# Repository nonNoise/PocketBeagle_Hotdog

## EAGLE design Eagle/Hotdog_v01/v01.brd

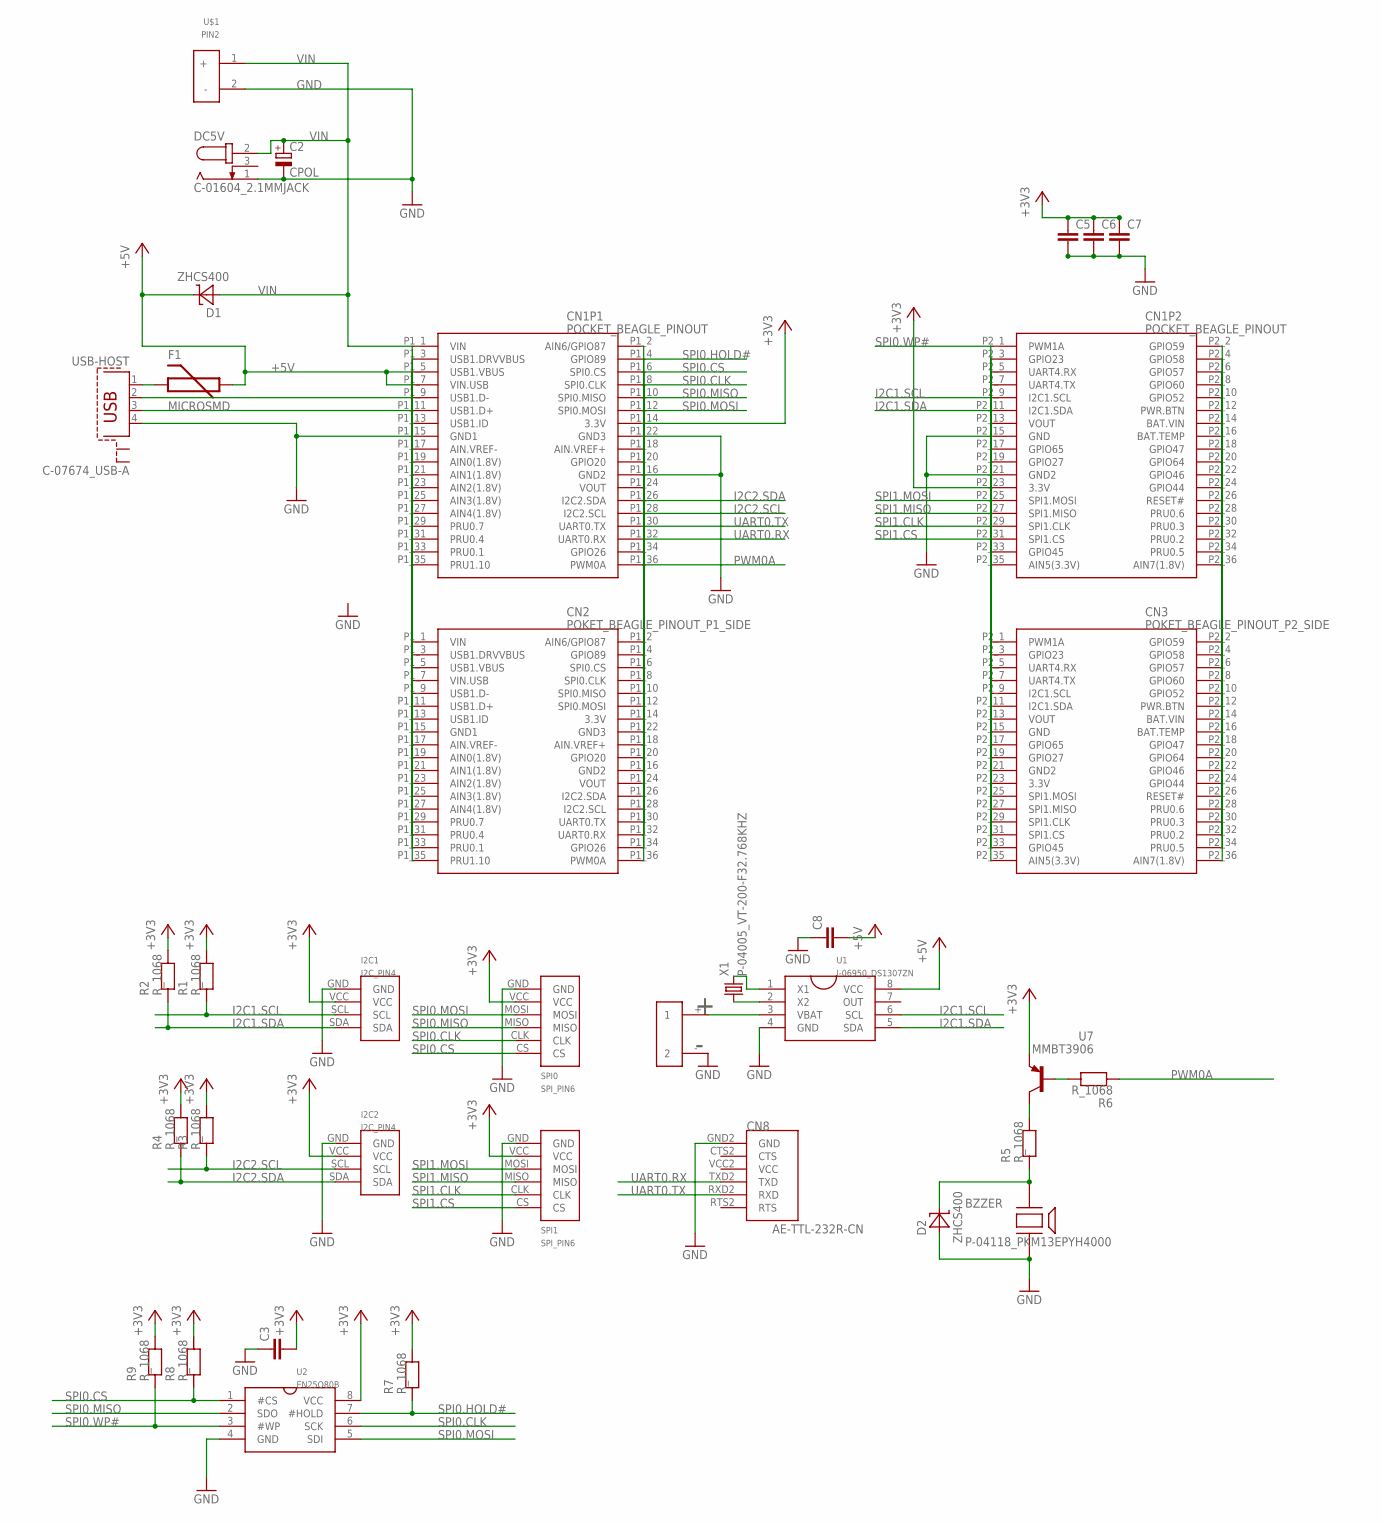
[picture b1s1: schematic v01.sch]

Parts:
BZZER: P-04118_PKM13EPYH4000; PKM13EPYH4000
C2: CPOL; 153CLV-0605
C3, C6, C7, C8: C_1068; C0603
C5: C_2012; C0805K
CN1: POCKET_BEAGLE_PINOUT
CN2: POKET_BEAGLE_PINOUT_P1_SIDE
CN3: POKET_BEAGLE_PINOUT_P2_SIDE
CN8: AE-TTL-232R-CN
CR2032: P-00706_CH25-2032LF; CH25-2032LF
D1, D2: ZHCS400; SOD323-W
DC5V: C-01604_2.1MMJACK; 2.1MMJACK
F1: MICROSMD
I2C1, I2C2: I2C_PIN4
R1, R2, R3, R4, R5, R6, R7, R8, R9: R_1068; R0603
SPI0, SPI1: SPI_PIN6
U1: I-06950_DS1307ZN; SO8
U2: EN25Q80B; SO8
U7: MMBT3906; SOT23
U$1: PIN2
USB-HOST: C-07674_USB-A; PN87520-S
X1: P-04005_VT-200-F32.768KHZ; VT-200F

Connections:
+3V3: C3.2, C5.1, C6.1, C7.1, CN1.P1_14 (3.3V), CN1.P2_23 (3.3V), CN2.P1_14 (3.3V), CN3.P2_23 (3.3V), I2C1.VCC, I2C2.VCC, R1.2, R2.2, R3.2, R4.2, R7.2, R8.2, R9.2, SPI0.VCC, SPI1.VCC, U2.8 (VCC), U7.2 (E)
+5V: C8.2, CN1.P1_5 (USB1.VBUS), CN1.P1_7 (VIN.USB), CN2.P1_5 (USB1.VBUS), CN2.P1_7 (VIN.USB), D1.C, F1.P$2, U1.8 (VCC)
GND: BZZER.2, C2.-, C3.1, C5.2, C6.2, C7.2, C8.1, CN1.P1_15 (GND1), CN1.P1_16 (GND2), CN1.P1_22 (GND3), CN1.P2_15 (GND), CN1.P2_21 (GND2), CN2.P1_15 (GND1), CN2.P1_16 (GND2), CN2.P1_22 (GND3), CN3.P2_15 (GND), CN3.P2_21 (GND2), CN8.GND2 (GND), CR2032.- (2), D2.A, DC5V.1 (GND), I2C1.GND, I2C2.GND, SPI0.GND, SPI1.GND, U1.4 (GND), U2.4 (GND), U$1.2 (-), USB-HOST.4
I2C1.SCL: CN1.P2_9 (I2C1.SCL), CN3.P2_9 (I2C1.SCL), I2C1.SCL, R1.1, U1.6 (SCL)
I2C1.SDA: CN1.P2_11 (I2C1.SDA), CN3.P2_11 (I2C1.SDA), I2C1.SDA, R2.1, U1.5 (SDA)
I2C2.SCL: CN1.P1_28 (I2C2.SCL), CN2.P1_28 (I2C2.SCL), I2C2.SCL, R3.1
I2C2.SDA: CN1.P1_26 (I2C2.SDA), CN2.P1_26 (I2C2.SDA), I2C2.SDA, R4.1
unnamed: CN1.P1_35 (PRU1.10), CN2.P1_35 (PRU1.10)
unnamed: CN1.P1_33 (PRU0.1), CN2.P1_33 (PRU0.1)
unnamed: CN1.P1_31 (PRU0.4), CN2.P1_31 (PRU0.4)
unnamed: CN1.P1_29 (PRU0.7), CN2.P1_29 (PRU0.7)
unnamed: CN1.P1_27 (AIN4(1.8V)), CN2.P1_27 (AIN4(1.8V))
unnamed: CN1.P1_25 (AIN3(1.8V)), CN2.P1_25 (AIN3(1.8V))
unnamed: CN1.P1_23 (AIN2(1.8V)), CN2.P1_23 (AIN2(1.8V))
unnamed: CN1.P1_21 (AIN1(1.8V)), CN2.P1_21 (AIN1(1.8V))
unnamed: CN1.P1_19 (AIN0(1.8V)), CN2.P1_19 (AIN0(1.8V))
unnamed: CN1.P1_17 (AIN.VREF-), CN2.P1_17 (AIN.VREF-)
unnamed: R5.2, U7.3 (C)
unnamed: BZZER.1, D2.C, R5.1
unnamed: CN1.P1_11 (USB1.D+), CN2.P1_11 (USB1.D+), USB-HOST.3
unnamed: CN1.P1_9 (USB1.D-), CN2.P1_9 (USB1.D-), USB-HOST.2
unnamed: CN1.P1_13 (USB1.ID), CN2.P1_13 (USB1.ID)
unnamed: R6.2, U7.1 (B)
unnamed: CN1.P1_3 (USB1.DRVVBUS), CN2.P1_3 (USB1.DRVVBUS)
unnamed: F1.P$1, USB-HOST.1
unnamed: CN1.P1_34 (GPIO26), CN2.P1_34 (GPIO26)
unnamed: CN1.P1_24 (VOUT), CN2.P1_24 (VOUT)
unnamed: CN1.P1_20 (GPIO20), CN2.P1_20 (GPIO20)
unnamed: CN1.P1_18 (AIN.VREF+), CN2.P1_18 (AIN.VREF+)
unnamed: CN1.P1_2 (AIN6/GPIO87), CN2.P1_2 (AIN6/GPIO87)
unnamed: CN1.P2_35 (AIN5(3.3V)), CN3.P2_35 (AIN5(3.3V))
unnamed: CN1.P2_33 (GPIO45), CN3.P2_33 (GPIO45)
unnamed: CN1.P2_19 (GPIO27), CN3.P2_19 (GPIO27)
unnamed: CN1.P2_17 (GPIO65), CN3.P2_17 (GPIO65)
unnamed: CN1.P2_13 (VOUT), CN3.P2_13 (VOUT)
unnamed: CN1.P2_7 (UART4.TX), CN3.P2_7 (UART4.TX)
unnamed: CN1.P2_5 (UART4.RX), CN3.P2_5 (UART4.RX)
unnamed: CN1.P2_3 (GPIO23), CN3.P2_3 (GPIO23)
unnamed: CN1.P2_36 (AIN7(1.8V)), CN3.P2_36 (AIN7(1.8V))
unnamed: CN1.P2_34 (PRU0.5), CN3.P2_34 (PRU0.5)
unnamed: CN1.P2_32 (PRU0.2), CN3.P2_32 (PRU0.2)
unnamed: CN1.P2_30 (PRU0.3), CN3.P2_30 (PRU0.3)
unnamed: CN1.P2_28 (PRU0.6), CN3.P2_28 (PRU0.6)
unnamed: CN1.P2_26 (RESET#), CN3.P2_26 (RESET#)
unnamed: CN1.P2_24 (GPIO44), CN3.P2_24 (GPIO44)
unnamed: CN1.P2_22 (GPIO46), CN3.P2_22 (GPIO46)
unnamed: CN1.P2_20 (GPIO64), CN3.P2_20 (GPIO64)
unnamed: CN1.P2_18 (GPIO47), CN3.P2_18 (GPIO47)
unnamed: CN1.P2_16 (BAT.TEMP), CN3.P2_16 (BAT.TEMP)
unnamed: CN1.P2_14 (BAT.VIN), CN3.P2_14 (BAT.VIN)
unnamed: CN1.P2_12 (PWR.BTN), CN3.P2_12 (PWR.BTN)
unnamed: CN1.P2_10 (GPIO52), CN3.P2_10 (GPIO52)
unnamed: CN1.P2_8 (GPIO60), CN3.P2_8 (GPIO60)
unnamed: CN1.P2_6 (GPIO57), CN3.P2_6 (GPIO57)
unnamed: CN1.P2_4 (GPIO58), CN3.P2_4 (GPIO58)
unnamed: CN1.P2_2 (GPIO59), CN3.P2_2 (GPIO59)
unnamed: U1.2 (X2), X1.1
unnamed: U1.1 (X1), X1.2
unnamed: CR2032.+ (1), U1.3 (VBAT)
PWM0A: CN1.P1_36 (PWM0A), CN2.P1_36 (PWM0A), R6.1
SPI0.CLK: CN1.P1_8 (SPI0.CLK), CN2.P1_8 (SPI0.CLK), SPI0.CLK, U2.6 (SCK)
SPI0.CS: CN1.P1_6 (SPI0.CS), CN2.P1_6 (SPI0.CS), R8.1, SPI0.CS, U2.1 (#CS)
SPI0.HOLD#: CN1.P1_4 (GPIO89), CN2.P1_4 (GPIO89), R7.1, U2.7 (#HOLD)
SPI0.MISO: CN1.P1_10 (SPI0.MISO), CN2.P1_10 (SPI0.MISO), SPI0.MISO, U2.2 (SDO)
SPI0.MOSI: CN1.P1_12 (SPI0.MOSI), CN2.P1_12 (SPI0.MOSI), SPI0.MOSI, U2.5 (SDI)
SPI0.WP#: CN1.P2_1 (PWM1A), CN3.P2_1 (PWM1A), R9.1, U2.3 (#WP)
SPI1.CLK: CN1.P2_29 (SPI1.CLK), CN3.P2_29 (SPI1.CLK), SPI1.CLK
SPI1.CS: CN1.P2_31 (SPI1.CS), CN3.P2_31 (SPI1.CS), SPI1.CS
SPI1.MISO: CN1.P2_27 (SPI1.MISO), CN3.P2_27 (SPI1.MISO), SPI1.MISO
SPI1.MOSI: CN1.P2_25 (SPI1.MOSI), CN3.P2_25 (SPI1.MOSI), SPI1.MOSI
UART0.RX: CN1.P1_32 (UART0.RX), CN2.P1_32 (UART0.RX), CN8.TXD2 (TXD)
UART0.TX: CN1.P1_30 (UART0.TX), CN2.P1_30 (UART0.TX), CN8.RXD2 (RXD)
VIN: C2.+, CN1.P1_1 (VIN), CN2.P1_1 (VIN), D1.A, DC5V.2 (VCC), U$1.1 (+)

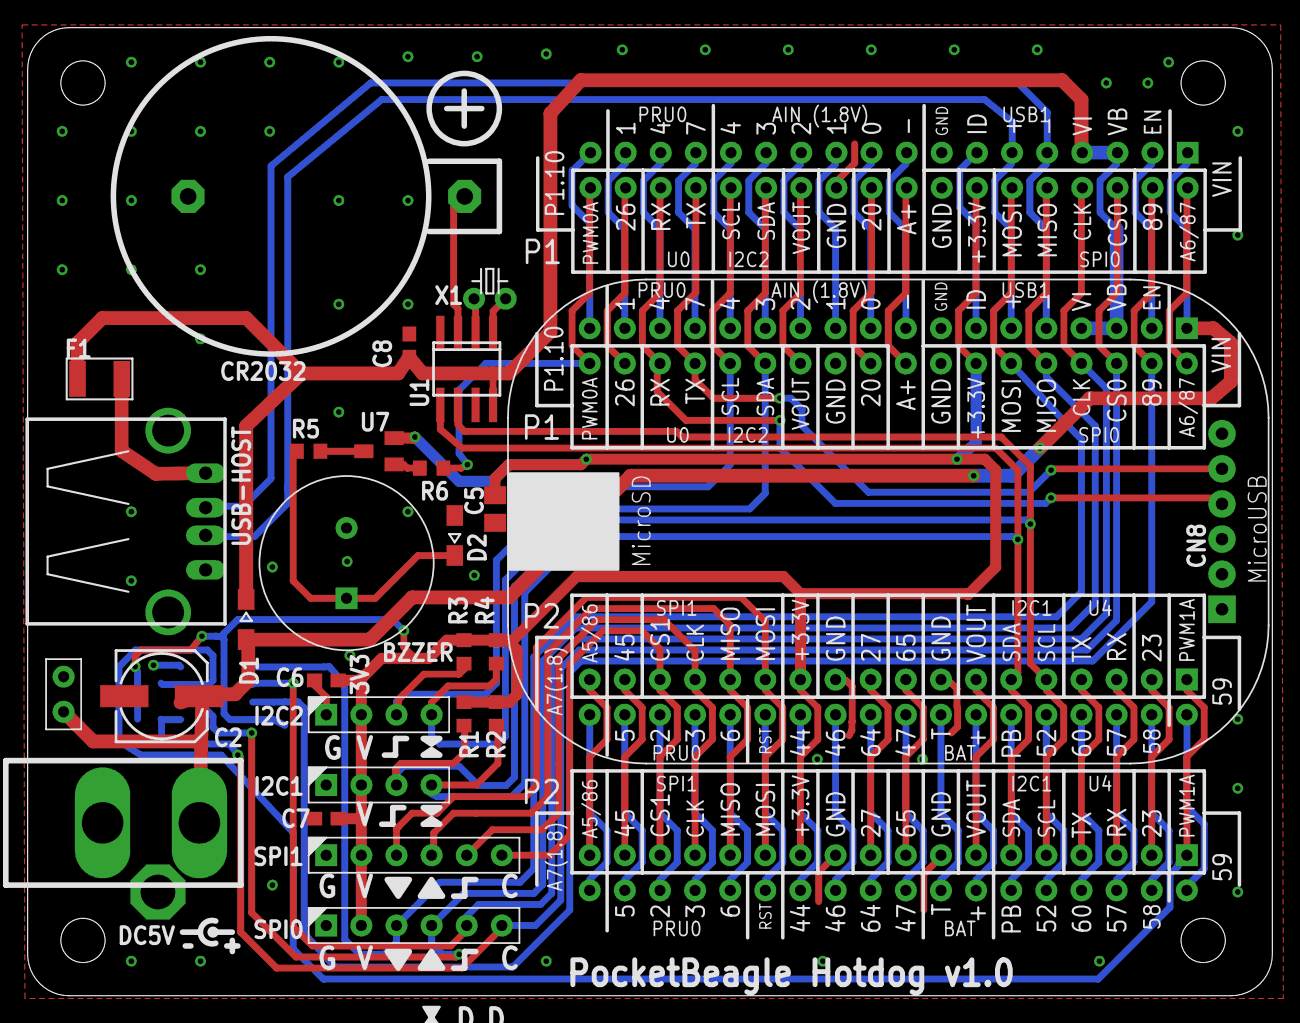
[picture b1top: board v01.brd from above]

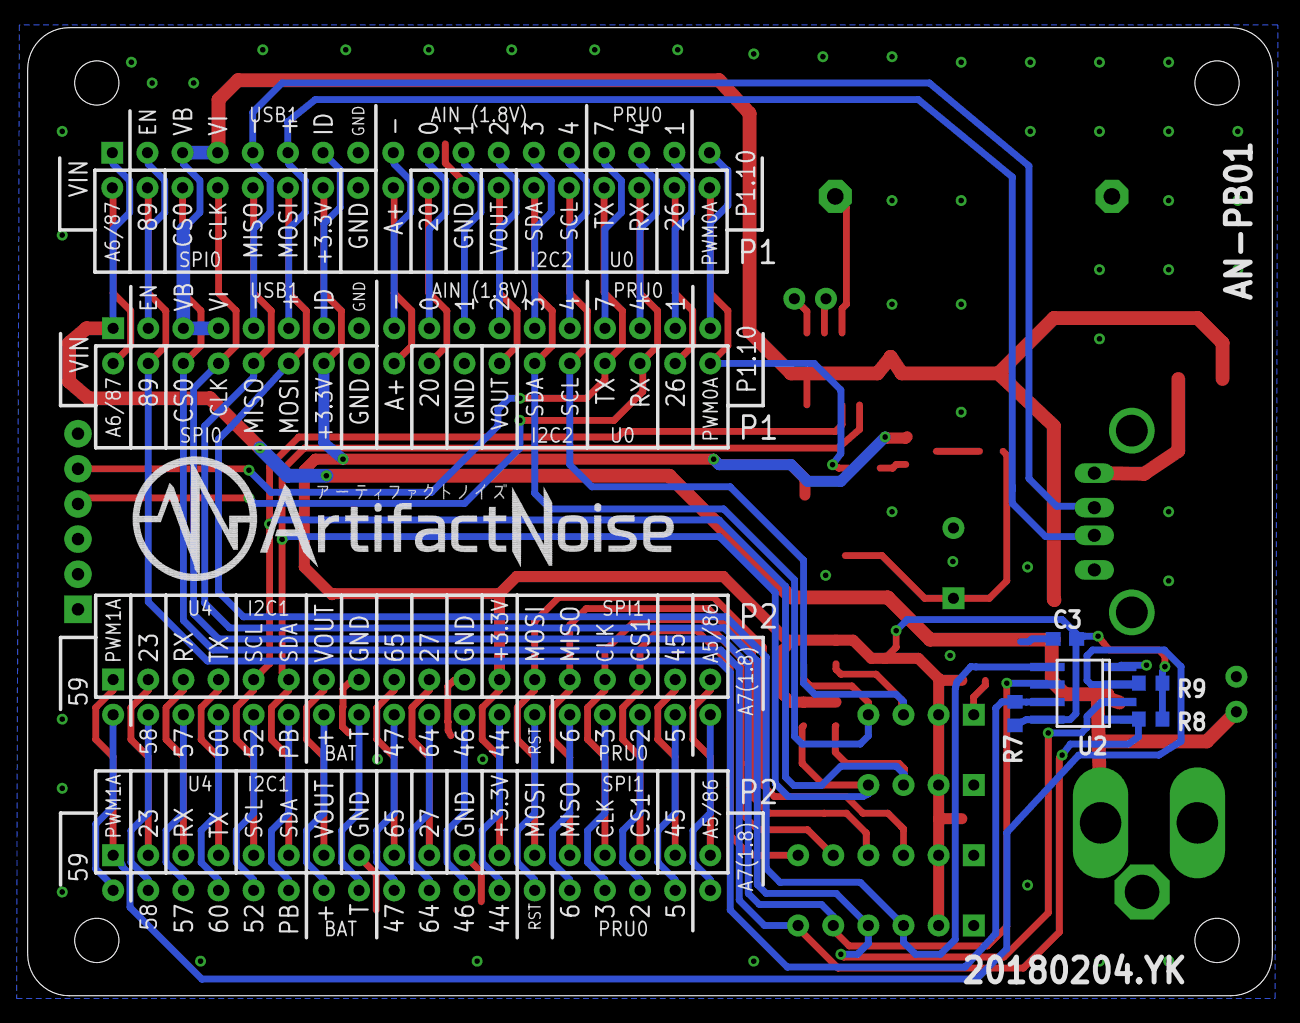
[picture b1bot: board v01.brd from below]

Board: 2 copper layers, 90.0 x 70.0 mm, 37 parts (6 on the bottom side), 73 nets.

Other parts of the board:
DRILEGEND: DRILEGEND
U$3: AN-POGO2_LITTLE_BIG
